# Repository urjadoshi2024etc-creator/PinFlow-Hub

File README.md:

# ⚡ PinFlow Hub | Engineering & PCB Design

Welcome to the central repository for **PinFlow Hub**. This is where I document my journey as an **Amateur Electronics & Telecommunication Engineering Student**, moving from messy breadboards to professional-grade hardware.

> **"Turning theoretical engineering into tangible hardware, one mistake at a time."**

---

## 📟 About the Project
PinFlow Hub is built for **aspiring engineers** who want to see the real side of electronics. No "perfect" expert tutorials here—just real learning, real debugging, and real projects.

### 🛠 Current Focus
* **Embedded Systems:** Working heavily with the **ESP32-S3**.
* **PCB Design:** Transitioning from through-hole to professional **SMD layouts** using KiCad.
* **Robotics:** Developing interactive desk companions and automated systems.

---

## 🚀 Active Projects
| Project | Description | Status |
| :--- | :--- | :--- |
| **Mochi Robot** | An ESP32-S3 based AI desk companion with a 3D interface. | In Progress 🛠 |
| **Touch Card PCB** | A sleek, professional capacitive touch card using TTP223. | Prototyping 🧪 |
| **Urja Inventory** | A Python-based system for tracking hardware components. | Beta 📁 |

---

## 🛠 Tech Stack & Tools
* **Design:** KiCad (PCB Design), Fusion 360 (3D Modeling)
* **Microcontrollers:** ESP32-S3, Arduino, STM32
* **Software:** C++, Python, Google Apps Script
* **Hardware:** SMD soldering (0805 focus), Logic Analyzers

---

## 📸 Join the Journey
I share the visual side of these builds, including the "Engineering Chaos" and lab vibes, on my social platforms:

* **Instagram:** [@pinflow.hub](https://www.instagram.com/pinflow.hub)
* **Pinterest:** [PinFlow Hub](https://in.pinterest.com/pinflowh)

---

## 🤝 Let's Connect
If you are a fellow student or an aspiring engineer, feel free to fork these projects and learn along with me! 

**Note:** Since I am an amateur student, please double-check schematics before ordering your own PCBs. Let's learn together!

---
## 🛠️ PinFlow Hub: Recommended Desk Setup

To build professional-grade PCBs like this, I recommend the following "Pro-Student" lab setup. These tools are selected for their precision in handling tiny SMD components and artistic PCB work.

| Category | Essential Tool | Link | Purpose |
| :--- | :--- | :--- | :--- |
| **🔌 Soldering** | **Precision Solder (0.6mm)** | [Buy Here 🛒](https://amzn.to/3OcU3Cd) | Perfect thickness for small 0805 pads. |
| | **Brass Tip Cleaner** | [Buy Here 🛒](https://amzn.to/48uirpR) | Cleans the iron tip without cooling it down. |
| | **Solder Wick (Braid)** | [Buy Here 🛒](https://amzn.to/4cuoMm3) | Essential for fixing solder bridges. |
| | **Helping Hands** | [Buy Here 🛒](https://amzn.to/42eUvmv) | Steady "Third Hand" with magnification. |
| **📐 Bench & Art** | **A1 Large Cutting Mat** | [Buy Here 🛒](https://amzn.to/42erB63) | 36"x24" Pro-size desk protection and grid. |
| | **A2 Medium Cutting Mat** | [Buy Here 🛒](https://amzn.to/4czzUyb) | 18"x24" Standard size—perfect for student desks. |
| | **ESD Safe Tweezers** | [Buy Here 🛒](https://amzn.to/4tkQ4Th) | **Green Edition:** Straight & Curved points for 0805 parts. |
| | **Detail Precision Knife** | [Buy Here 🛒](https://amzn.to/4dWvh3I) | For PCB trace cutting and precision art work. |
| | **Micro Flush Cutters** | [Buy Here 🛒](https://amzn.to/3Z0Z5Xy) | Cleanly trims legs for a professional finish. |
| **📟 Logic & Test** | **Budget Multimeter** | [Buy Here 🛒](https://amzn.to/41COznj) | Best for basic continuity "Beep" tests. |
| | **Pro Multimeter** | [Buy Here 🛒](https://amzn.to/4tjIicd) | High-precision debugging for serious designers. |
| | **N-Channel MOSFETs** | [Buy Here 🛒](https://amzn.to/4teYcEI) | Logic-level switching for "No-Code" projects. |

---
> *Disclaimer: These are affiliate links. Using them supports PinFlow Hub in developing more free open-source hardware!* 🚀
---
*MIT License © 2026 PinFlow Hub*

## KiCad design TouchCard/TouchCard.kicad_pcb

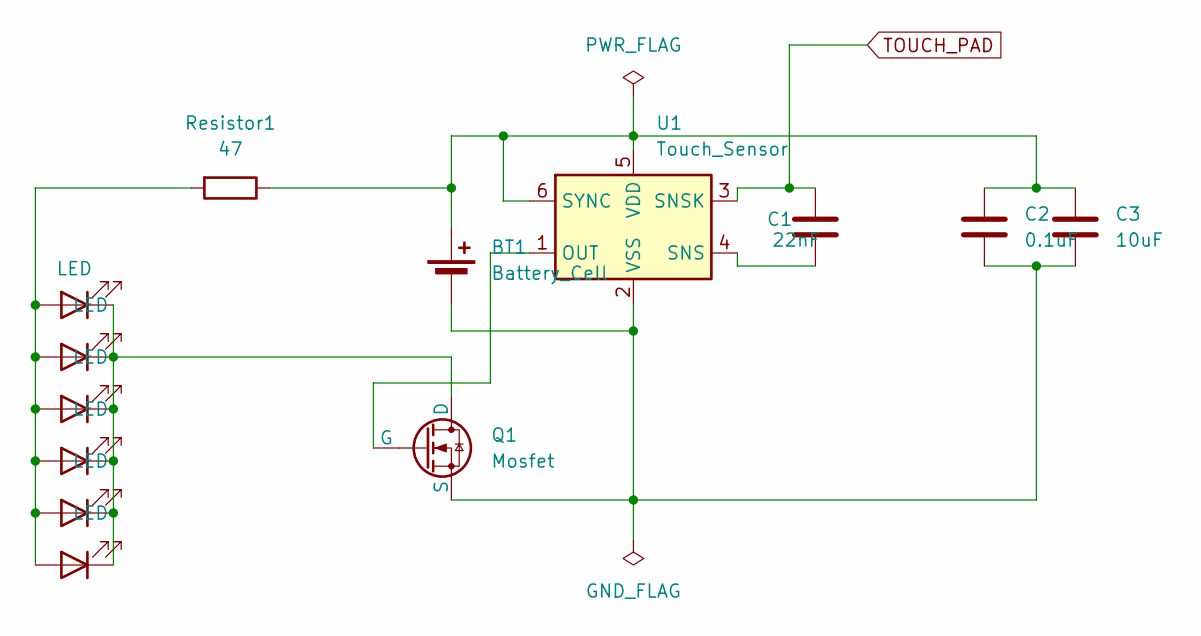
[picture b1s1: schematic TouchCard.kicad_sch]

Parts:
BT1: Battery_Cell; BatteryHolder_Keystone_1060_1x2032
C1: 22nF; C_0805_2012Metric
C2: 0.1uF; C_0805_2012Metric
C3: 10uF; C_0805_2012Metric
D1, D2, D3, D4, D5, D6: LED; LED_0805_2012Metric
Q1: Mosfet; SOT-23
Resistor1: 47; R_0805_2012Metric
U1: Touch_Sensor; SOT-23-6

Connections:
unnamed 0: BT1.1 (+), C2.1, C3.1, Resistor1.1, U1.5 (VDD), U1.6 (SYNC); also elsewhere on the board
unnamed: BT1.2 (-), C2.2, C3.2, Q1.2 (S), U1.2 (VSS)
unnamed 2: D1.2 (A), D2.2 (A), D3.2 (A), D4.2 (A), D5.2 (A), D6.2 (A), Resistor1.2; also elsewhere on the board
unnamed: D1.1 (K), D2.1 (K), D3.1 (K), D4.1 (K), D5.1 (K), D6.1 (K), Q1.3 (D)
unnamed: Q1.1 (G), U1.1 (OUT)
unnamed: C1.2, U1.4 (SNS)
TOUCH_PAD: C1.1, U1.3 (SNSK)

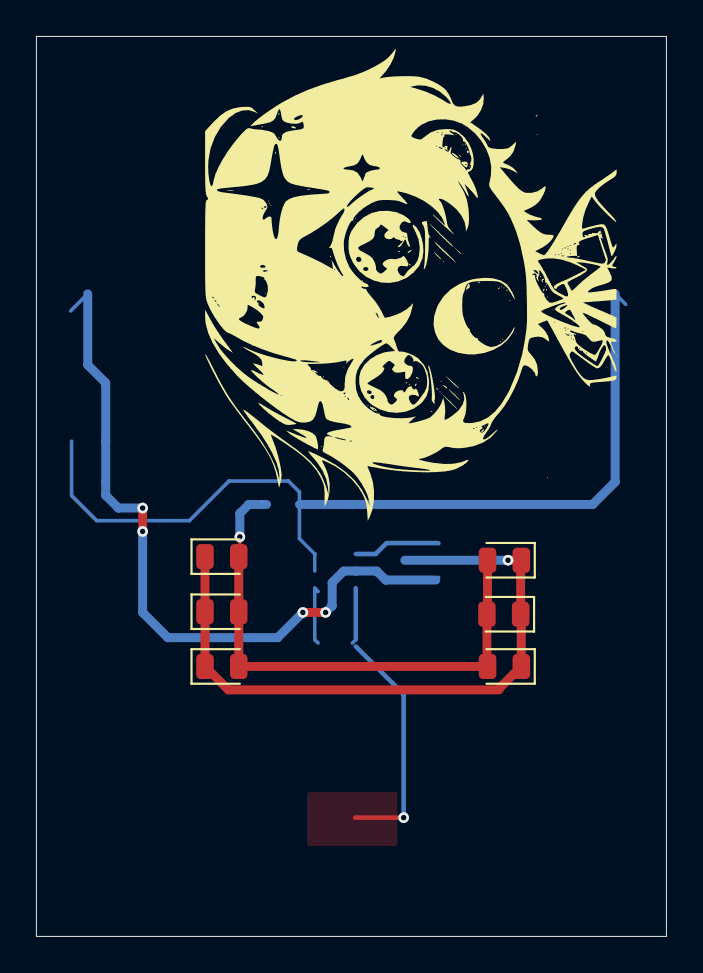
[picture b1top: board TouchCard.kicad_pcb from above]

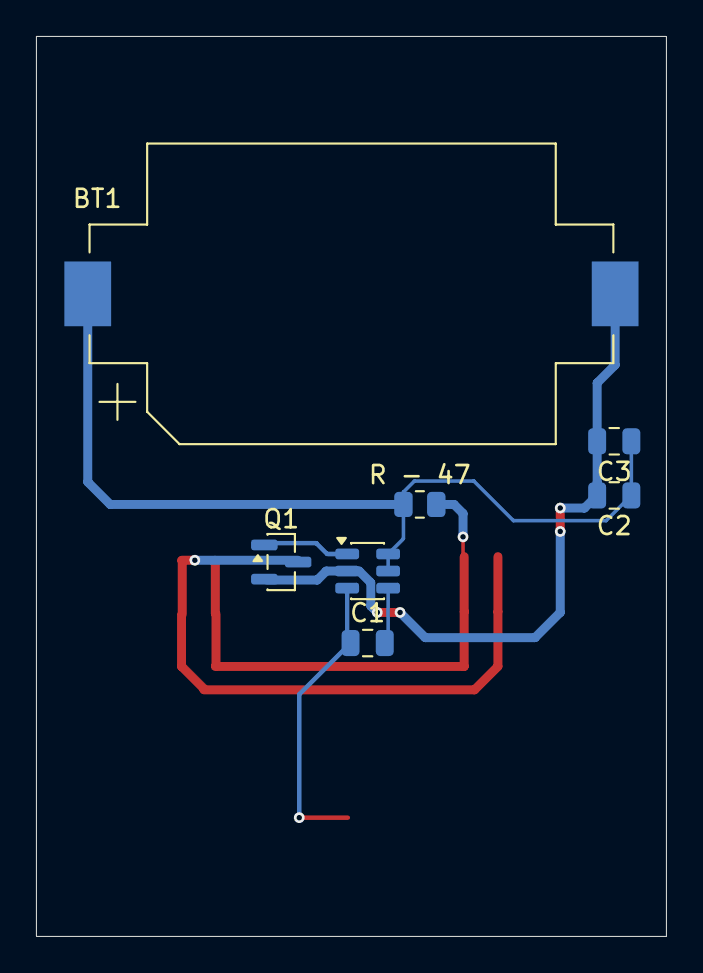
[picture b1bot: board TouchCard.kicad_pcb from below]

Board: 2 copper layers, 35.0 x 50.0 mm, 13 parts (7 on the bottom side), 7 nets.

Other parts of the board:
R - 47: 47; R_0805_2012Metric

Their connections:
unnamed 0: R - 47.1; also elsewhere on the board
unnamed 2: R - 47.2; also elsewhere on the board

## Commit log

2026-04-18 Revise README for enhanced project documentation
    Updated the README to provide a more detailed overview of the PinFlow Hub, including sections on current projects, tech stack, and social media links.
2026-04-18 Update .gitignore to include local history files
2026-04-18 Add KiCad.gitignore file
2026-04-18 Create TouchCard.md with project overview and details
    Added documentation for the Professional Hardware Interface Card, detailing features, usage instructions, and repository structure.
2026-04-18 Revise TouchCard.md with enhanced project details
    Updated the TouchCard documentation with new sections on project objectives, technical specifications, engineering design decisions, and usage instructions.
2026-04-18 Revise TouchCard project overview and objectives
    Enhanced project description with detailed objectives, ideas, and technical explorations.
2026-04-18 Add recommended tools and components section
    Added a section for recommended tools and components for the project.
2026-04-18 Update README with recommended lab setup and tools
    Added a recommended lab setup section with tools and links for soldering, assembly, measurement, and debugging.
2026-04-18 Revise recommended desk setup for PCB tools
    Updated the recommended desk setup section with essential tools for PCB assembly and soldering. Removed the previous lab setup section for clarity.
2026-04-19 Enhance desk setup recommendations for PCB work
    Updated the recommended desk setup section to include additional tools for artistic PCB work and replaced the Green Grid Mat with A1 and A2 Cutting Mats.
